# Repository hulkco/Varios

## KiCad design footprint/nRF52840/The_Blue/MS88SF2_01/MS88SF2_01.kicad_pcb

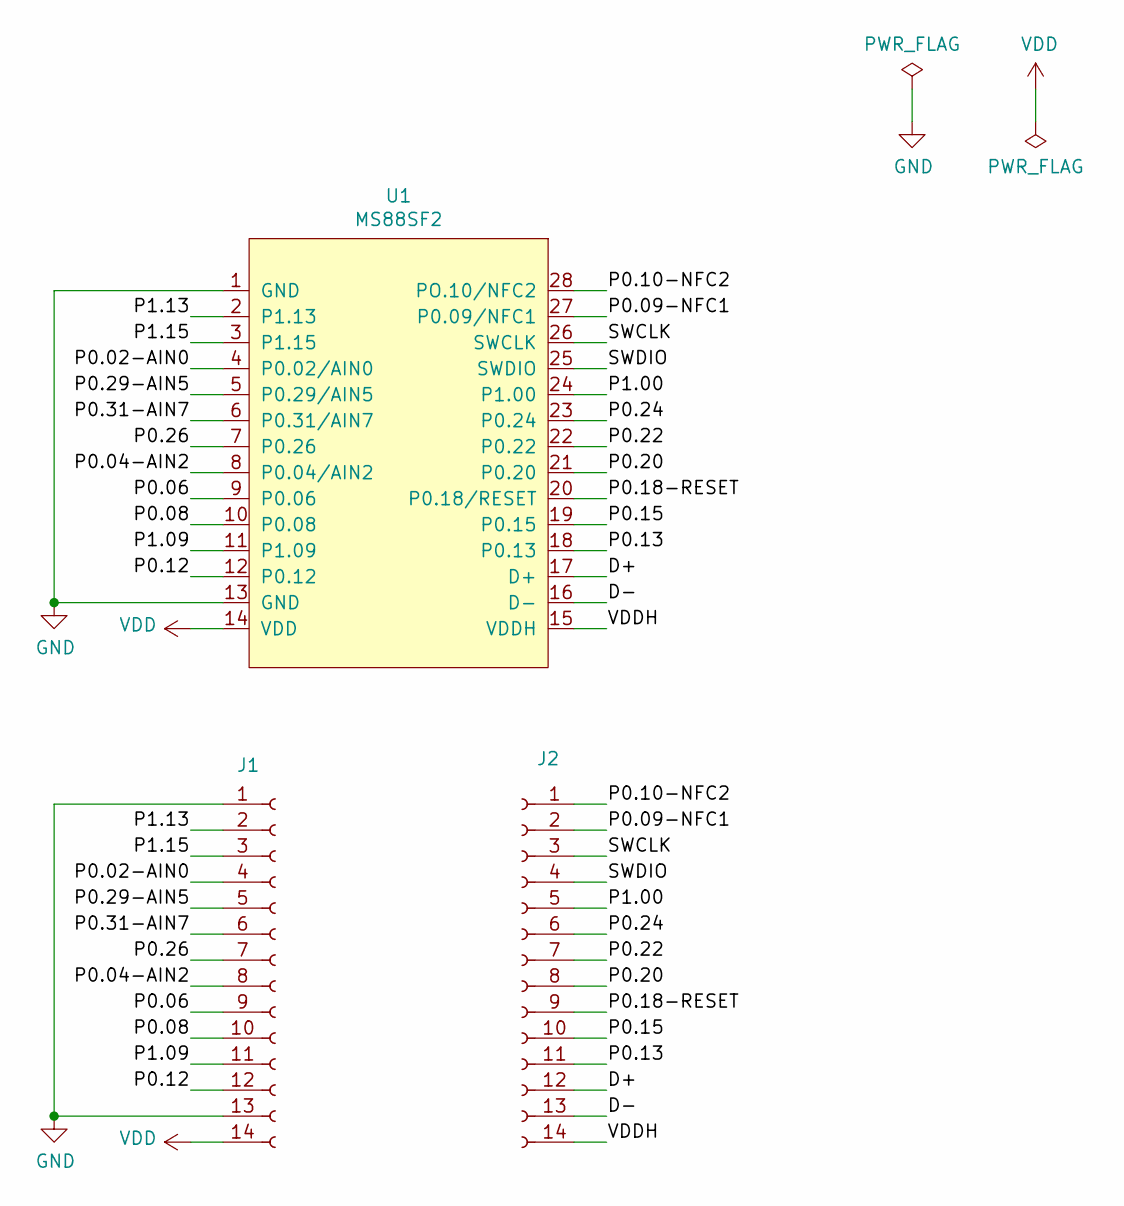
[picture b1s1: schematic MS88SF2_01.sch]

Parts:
J1, J2: Conn_01x14_Female; PinSocket_1x14
U1: MS88SF2

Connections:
/D+: J2.12, U1.17 (D+)
/D-: J2.13, U1.16 (D-)
/P0.02-AIN0: J1.4, U1.4 (P0.02/AIN0)
/P0.04-AIN2: J1.8, U1.8 (P0.04/AIN2)
/P0.06: J1.9, U1.9 (P0.06)
/P0.08: J1.10, U1.10 (P0.08)
/P0.09-NFC1: J2.2, U1.27 (P0.09/NFC1)
/P0.10-NFC2: J2.1, U1.28 (PO.10/NFC2)
/P0.12: J1.12, U1.12 (P0.12)
/P0.13: J2.11, U1.18 (P0.13)
/P0.15: J2.10, U1.19 (P0.15)
/P0.18-RESET: J2.9, U1.20 (P0.18/RESET)
/P0.20: J2.8, U1.21 (P0.20)
/P0.22: J2.7, U1.22 (P0.22)
/P0.24: J2.6, U1.23 (P0.24)
/P0.26: J1.7, U1.7 (P0.26)
/P0.29-AIN5: J1.5, U1.5 (P0.29/AIN5)
/P0.31-AIN7: J1.6, U1.6 (P0.31/AIN7)
/P1.00: J2.5, U1.24 (P1.00)
/P1.09: J1.11, U1.11 (P1.09)
/P1.13: J1.2, U1.2 (P1.13)
/P1.15: J1.3, U1.3 (P1.15)
/SWCLK: J2.3, U1.26 (SWCLK)
/SWDIO: J2.4, U1.25 (SWDIO)
/VDDH: J2.14, U1.15 (VDDH)
GND: J1.1, J1.13, U1.1 (GND), U1.13 (GND)
VDD: J1.14, U1.14 (VDD)

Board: 2 copper layers, 3 parts (0 on the bottom side), 27 nets, no tracks yet.

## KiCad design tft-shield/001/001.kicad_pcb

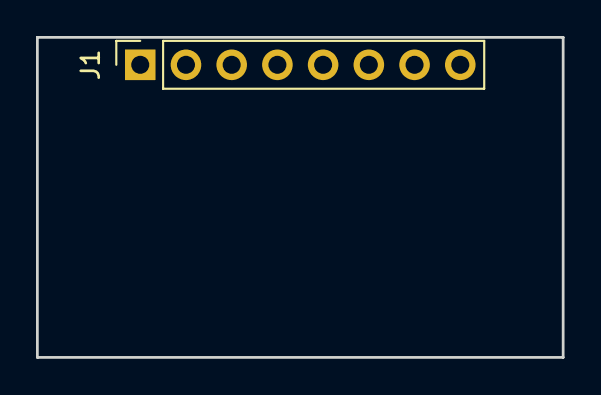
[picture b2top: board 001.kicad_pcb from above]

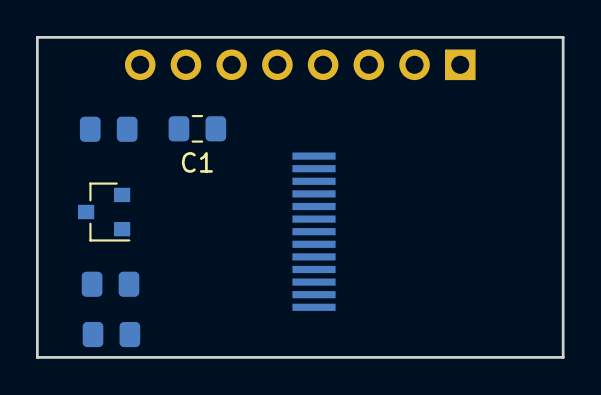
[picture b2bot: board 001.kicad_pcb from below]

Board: 2 copper layers, 29.2 x 17.8 mm, 7 parts (6 on the bottom side), 12 nets, no tracks yet.

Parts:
C1: 1uF; C_0805_2012Metric_Pad1.15x1.40mm_HandSolder
J1: CONN_01X08; PinSocket_1x08_P2.54mm_Vertical
Q1: S8050; SOT-23
R1: 1k; R_0805_2012Metric_Pad1.15x1.40mm_HandSolder
R2: 10k; R_0805_2012Metric_Pad1.15x1.40mm_HandSolder
R3: 10ohm; R_0805_2012Metric_Pad1.15x1.40mm_HandSolder
U1: TFT_0.9680*160; TFT_0.96_SPI

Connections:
/BLK: J1.3, R1.2
/CS: J1.4, U1.7
/DC: J1.6, U1.5
/LEDK: R3.1, U1.11
/RES: J1.5, U1.6
/SCL: J1.7, U1.4
/SDA: J1.8, U1.3
GND: C1.2, J1.1, Q1.1, U1.8, U1.13
unnamed: C1.1, U1.10
unnamed: Q1.2, R1.1, R2.1
unnamed: Q1.3, R3.2
VCC: J1.2, R2.2, U1.12
